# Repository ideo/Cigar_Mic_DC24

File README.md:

### Cigar Mic
Designed for DEF CON 24 to compliment the [Bender Badge by AND!XOR](https://github.com/ANDnXOR/ANDnXOR_DC24_Badge). The Cigar Mic adds an audio input to the Bender Badge in order to show a real-time spectrum anaysis of any activity occuring between 0 and 10kHz around the badge.

#### Configuration
Cigar mic requires 3.3V, GND, an ADC input pin, and three 3.3V output pins. The included software is compatible with AND!XOR’s Bender Badge and should be connected as follows:
```
OUT  -> PA1
GND  -> GND
3.3V -> 3.3V
L1   -> PA3
L2   -> PA4
L3   -> PA5
```

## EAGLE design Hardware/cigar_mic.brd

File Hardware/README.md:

### Cigar Mic Hardware
Schematic and layout created using [Eagle 7.4.0](https://cadsoft.io/)

The Cigar Mic is a fairly simple analog device comprised of a microphone, an amplifier, and a low pass filter. The cutoff frequency of the LPF is ~10kHz and the gain of the amplifier is 100. The circuit requires and 3.3V source, and the output signal is centered around ~1.65V.

The top side of the board includes 3 orange LEDs that run at 20mA each (this is very bright, and I’d suggest raising the value of their resistors, R7,8,9, to make the LEDs a little more subtle). These are positioned to make it look like the cigar is lit.

This layout differs slightly from what was released at DEF CON 24 in order to fix two errors with the original design. The first being the + and - flipped, hence the flywires soldered to these pins, and the other being the mic leads were flipped. Both of these were a result of quick design and not paying attention/double checking parts designed by others.

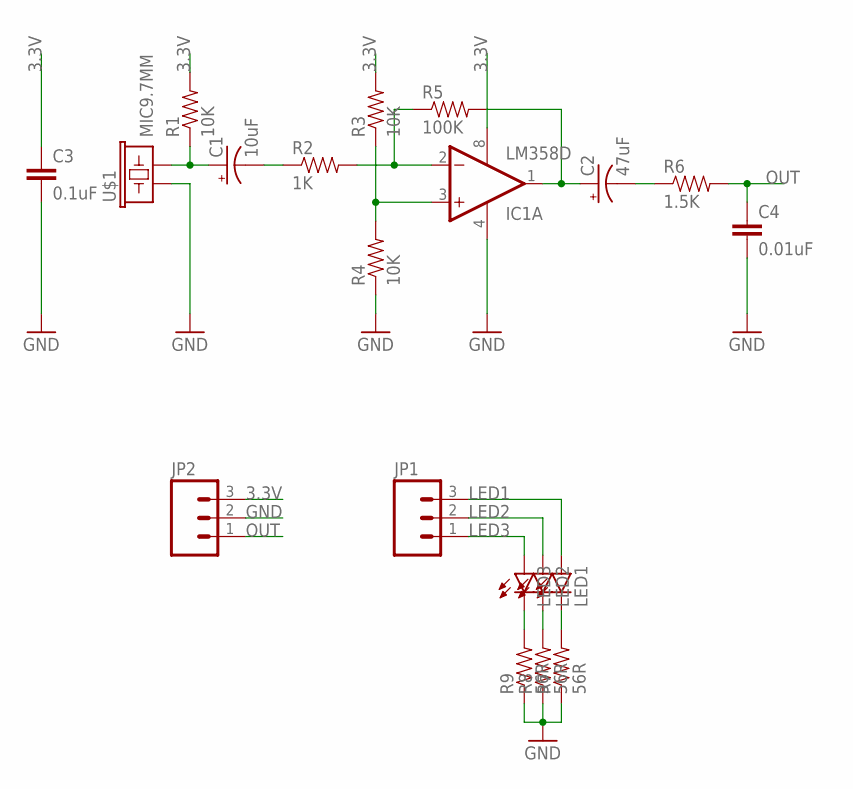
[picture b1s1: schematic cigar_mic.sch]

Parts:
C1: 10uF; POLAR
C2: 47uF; POLAR
C3: 0.1uF; 0805
C4: 0.01uF; 0805
IC1: LM358D; SO08
JP1, JP2: M031X03_NO_SILK; 1X03_NO_SILK
LED1, LED2, LED3: LED0603; LED-0603
R1, R3, R4: 10K; 0603-RES
R2: 1K; 0603-RES
R5: 100K; 0603-RES
R6: 1.5K; 0603-RES
R7, R8, R9: 56R; 0603-RES
U$1: MIC9.7MM; MIC-9.7MM

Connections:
3.3V: C3.1, IC1.8 (V+), JP2.3, R1.2, R3.2
GND: C3.2, C4.2, IC1.4 (V-), JP2.2, R4.1, R7.1, R8.1, R9.1, U$1.1
LED1: JP1.3, LED1.A
LED2: JP1.2, LED2.A
LED3: JP1.1, LED3.A
unnamed: C1.P$1 (+), R1.1, U$1.2
unnamed: C1.P$2 (-), R2.1
unnamed: IC1.2 (-IN), R2.2, R5.1
unnamed: IC1.3 (+IN), R3.1, R4.2
unnamed: C2.P$1 (+), IC1.1 (OUT), R5.2
unnamed: C2.P$2 (-), R6.1
unnamed: LED3.C, R9.2
unnamed: LED2.C, R8.2
unnamed: LED1.C, R7.2
OUT: C4.1, JP2.1, R6.2

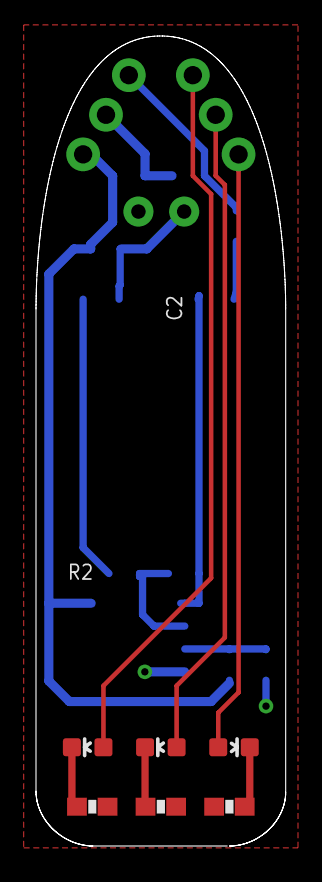
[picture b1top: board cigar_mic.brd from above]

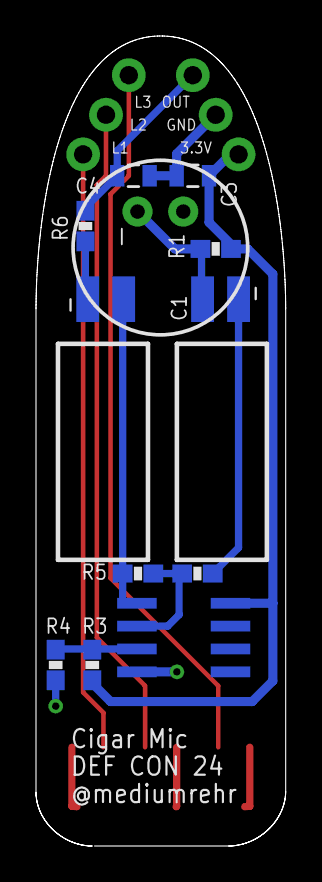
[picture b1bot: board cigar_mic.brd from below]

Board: 2 copper layers, 13.9 x 45.0 mm, 20 parts (12 on the bottom side), 15 nets.

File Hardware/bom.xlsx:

| Cigar Mic v1
 | Rob Rehr
 | DEF CON 24
 | Aug 4, 2016
 | Item | Reference | Package | Description | Manufacturer | Part # | Distributor | Distributor Part #
 |  | IC1 | 8-SO | IC OPAMP GP 1.1MHZ 8SO | STMicroelectronics | LM358DT | DigiKey | 497-1591-1-ND
 |  | U$1 | TH | 20Hz ~ 20kHz Analog Microphone Electret Condenser Omnidirectional (-44dB ±2dB @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 | CUI Inc | CMA-4544PF-W | DigiKey | 102-1721-ND
 |  | R1,3,4 | 603 | RES SMD 10K OHM 5% 1/4W 0603 | Rohm Semiconductor | ESR03EZPJ103 | DigiKey | RHM10KDCT-ND
 |  | R2 | 603 | RES SMD 1K OHM 5% 1/4W 0603 | Rohm Semiconductor | ESR03EZPJ102 | DigiKey | RHM1.0KDCT-ND
 |  | R5 | 603 | RES SMD 100K OHM 5% 1/4W 0603 | Rohm Semiconductor | ESR03EZPJ104 | DigiKey | RHM100KDCT-ND
 |  | R6 | 603 | RES SMD 1.5K OHM 5% 1/4W 0603 | Rohm Semiconductor | ESR03EZPJ152 | DigiKey | RHM1.5KDCT-ND
 |  | R7,8,9 | 603 | RES SMD 56 OHM 5% 1/4W 0603 | Rohm Semiconductor | ESR03EZPJ560 | DigiKey | RHM56DCT-ND
 |  | C1 | TH | 10µF 25V Aluminum Capacitors Radial, Can 1000 Hrs @ 85°C | Elna America | RFS-25V100ME3#5 | DigiKey | 604-1050-ND
 |  | C2 | TH | 47µF 6.3V Aluminum Capacitors Radial, Can 2000 Hrs @ 105°C | Nichicon | UKA0J470MDD1TD | DigiKey | 493-4626-1-ND
 |  | C3 | 805 | 0.10µF 50V Ceramic Capacitor X7R 0805 (2012 Metric) 0.079" L x 0.049" W (2.00mm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 | TDK Corporation | C2012X7R1H104K085AA | DigiKey | 445-7534-1-ND
 |  | C4 | 805 | 10000pF 250V Ceramic Capacitor JB 0805 (2012 Metric) 0.079" L x 0.049" W (2.00m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 | TDK Corporation | C2012JB2E103K125AA | DigiKey | 445-11562-1-ND

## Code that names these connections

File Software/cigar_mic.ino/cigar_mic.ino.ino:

////////////////////////////////////////////////////////////////////
//
//  Real-time spectrum analyzer for 0-20kHz
//   
//  Designed for DEF CON 24 and AND!XOR's Bender Badge
//
//  1024-point FFT
//  ~40kHz sampling rate
//
//  Hardware and software developed by rob rehr (@mediumrehr)
//  Last modified: Aug 16, 2016
//
//  To Do:
//  - find/fix the error with showing the audio wave in DFU mode
//  - further test windowing function
//  - integrate with AND!XOR Bender Badge code
//    - reduce SRAM usage
//
//  MIT License
//
//  Credits
//  FFT library written by STMicroelectronics
//  Software based on projects by Beherith and pingumacpenguin
//
////////////////////////////////////////////////////////////////////

//-FFT-------------------------------------------------------------------------
#define FFTLEN 1024
#define LOGSCALE 1 // display bins logarithmicallly
#define LINSCALE 0 // display bins linearly
#include <cr4_fft_1024_stm32.h>
uint16_t data16[FFTLEN];
uint32_t data32[FFTLEN];
uint32_t y[FFTLEN];
uint16_t hammingwindow[FFTLEN/2];
// my best attempt at logarithmically spacing 511 bins
uint16_t logBins[32] = {0,1,2,3,4,5,6,7,8,9,10,11,12,13,15,18,22,27,33,40,49,59,72,87,106,129,156,190,230,280,340,413};
uint16_t logBinsGap[32] = {1,1,1,1,1,1,1,1,1,1,1,1,1,2,3,4,5,6,7,9,10,13,15,19,23,27,34,40,50,60,73,98};
uint16_t FFTMode = 1; // 1 for frequecy display; 0 for amplitude display

//-Display---------------------------------------------------------------------
#include <Adafruit_GFX_AS.h>
#include <Adafruit_SSD1306_STM32.h>
#include <SPI.h>

#define SCREENWIDTH 128
#define SCREENHEIGHT 64

#define OLED_MOSI  PB15
#define OLED_CLK   PB13
#define OLED_DC    PB3
#define OLED_CS    PB12
#define OLED_RESET PB4
Adafruit_SSD1306 display(OLED_MOSI, OLED_CLK, OLED_DC, OLED_RESET, OLED_CS);

//-DMA-------------------------------------------------------------------------
volatile static bool dma1_ch1_Active;
#include <libmaple/pwr.h>
#include <libmaple/scb.h>
#include <libmaple/rcc.h>
#include <libmaple/adc.h>

//-Other-----------------------------------------------------------------------
// cigar LEDs
#define LED1 PA3
#define LED2 PA4
#define LED3 PA5
#define LEDThresh 200
const int8_t analogInPin = PA1;
uint16_t ampWave[SCREENWIDTH] = {0};

void init_hamming_window(uint16_t *windowtarget, int len) {
  for(int i=0; i<len/2; i++){ windowtarget[i] = (0.54-0.46*cos((2*i*3.141592)/(len-1)))*65536; }
}

// not certain windowing is working correctly. more testing is needed
void window(uint32_t *data, uint16_t *weights, int len, int scale) {
  for(int i=0; i<len; i++){
    int weight_index = i;
    if(i >= len/2) weight_index = (len-1)-i;
    data[i] = ((data[i]*scale*weights[weight_index]) >> 16) & 0xFFFF;
  }
}

uint16_t asqrt(uint32_t x) {
  /*   From http://medialab.freaknet.org/martin/src/sqrt/sqrt.c
   *   Logically, these are unsigned. We need the sign bit to test
   *   whether (op - res - one) underflowed.
   *   good enough precision; 10x faster than regular sqrt
   */
  int32_t op, res, one;

  op = x;
  res = 0;
  /* "one" starts at the highest power of four <= than the argument. */
  one = 1 << 30;   /* second-to-top bit set */
  while(one > op) one >>= 2;
  while(one != 0) {
    if(op >= res+one) {
      op = op-(res+one);
      res = res+2*one;
    }
    res /= 2;
    one /= 4;
  }
  return (uint16_t)(res);
}

void fill(uint32_t *data, uint32_t value, int len) {
  for(int i=0; i<len; i++) { data[i] = value; }
}

void fill(uint16_t *data, uint32_t value, int len) {
  for(int i=0; i<len; i++) { data[i] = value; }
}

void real_to_complex(uint16_t *in, uint32_t *out, int len) {
  for(int i=0; i<len; i++) { out[i] = in[i]*8; }
}

void setADCs () {
  rcc_set_prescaler(RCC_PRESCALER_ADC, RCC_ADCPRE_PCLK_DIV_8 );

  int pinMapADCin = PIN_MAP[analogInPin].adc_channel;
  adc_set_sample_rate(ADC1, ADC_SMPR_239_5); // ~37.65 khz sample rate
 
  adc_set_reg_seqlen(ADC1, 1);
  ADC1->regs->SQR3 = pinMapADCin;
  ADC1->regs->CR2 |= ADC_CR2_CONT; // set continuous mode
  ADC1->regs->CR2 |= ADC_CR2_SWSTART; // regular channels
}

static void DMA1_CH1_Event() {
  dma1_ch1_Active = 0;
}

void adc_dma_enable(const adc_dev *dev) {
  bb_peri_set_bit(&dev->regs->CR2, ADC_CR2_DMA_BIT, 1);
}

void takeSamples() {
  if(FFTMode) {
    // perform DMA, 
    dma_init(DMA1);
    dma_attach_interrupt(DMA1, DMA_CH1, DMA1_CH1_Event);

    adc_dma_enable(ADC1);
    dma_setup_transfer(DMA1, DMA_CH1, &ADC1->regs->DR, DMA_SIZE_16BITS, data16, DMA_SIZE_16BITS, (DMA_MINC_MODE | DMA_TRNS_CMPLT)); // receive buffer DMA
    dma_set_num_transfers(DMA1, DMA_CH1, FFTLEN);
    dma1_ch1_Active = 1;
  
    dma_enable(DMA1, DMA_CH1); // enable the channel and start the transfer.
    uint32_t time_left_in_dma = micros();
  
    while(dma1_ch1_Active){ }; // wait for the DMA to complete
    dma_disable(DMA1, DMA_CH1); // end of trasfer, disable DMA and continuous mode.
    real_to_complex(data16, data32, FFTLEN);
    perform_fft(data32, y, FFTLEN);
    displayBins(y, FFTLEN, LOGSCALE);
  } else {
    // only works for serial upload. doesn't work with DFU mode for some reason
    int analogIn = analogRead(analogInPin);
    displayWave(analogIn);
  }
}

void setup() {
  // enable Serial
  Serial.begin(115200); // only works with serial upload mode
  
  // initialize the display
  display.begin(SSD1306_SWITCHCAPVCC);
  display.clearDisplay();
  display.display();

  // initialize FFT variables
  init_hamming_window(hammingwindow, FFTLEN);
  fill(y,0,FFTLEN);
  fill(data32,1,FFTLEN);
  fill(data16,1,FFTLEN);

  // calibrate and setup ADC
  adc_calibrate(ADC1);
  setADCs();

  // initialize cigar LEDs
  pinMode(LED1, OUTPUT);
  pinMode(LED2, OUTPUT);
  pinMode(LED3, OUTPUT);
  digitalWrite(LED1, LOW);
  digitalWrite(LED2, LOW);
  digitalWrite(LED3, LOW);
}

void inplace_magnitude(uint32_t *target, uint16_t len){
  uint16_t * p16;
  for(int i=0; i<len; i++){
     int16_t real = target[i] & 0xFFFF;
     int16_t imag = target[i] >> 16;
     uint32_t magnitude = asqrt(real*real + imag*imag);
     target[i] = magnitude; 
  }
}
  
uint32_t perform_fft(uint32_t *indata, uint32_t *outdata, const int len){
	uint32_t timetaken = micros();
//	window(indata,hammingwindow,len,1); //scaling factor of 4 for 4095> 16 bits
	cr4_fft_1024_stm32(outdata, indata, len);
	inplace_magnitude(outdata, len);
	return micros() - timetaken;
}

// dispaly audio as an amplitude wave
// only works with serial upload mode
void displayWave(uint16_t newAnalog) {
  display.clearDisplay();
  // move previous amplitudes forward
  for(int i=(SCREENWIDTH-1); i>0; i--) {
    display.drawLine(i, (32-ampWave[i-1]), i, (32+ampWave[i-1]), WHITE);
    ampWave[i] = ampWave[i-1];
  }
  // append newest applitude
  int newAmp = newAnalog*SCREENHEIGHT/4096;
  newAmp -= 32;
  display.drawLine(0, 32-newAmp, 0, 32+newAmp, WHITE);
  ampWave[0] = newAmp;
  display.display();
}

// display audio as bin levels after FFT
void displayBins(uint32_t *data, int len, bool scale) {
  uint32_t maxvalue = 1024;
  uint32_t myBins[32] = {0};
  uint32_t LED1Max = 0;
  uint32_t LED2Max = 0;
  uint32_t LED3Max = 0;
  if(scale) {
    // logarithmic x axis
    for(int i=0; i<32; i++) {
      myBins[i] = 0;
      for(int j=0; j<logBinsGap[i]; j++) {
        int newData = data[logBins[i]+j];
        myBins[i] = max(myBins[i], newData);
      }
    }
  } else {
    // linear x axis
    for(int i=0; i<32; i++) {
      myBins[i] = 0;
      for(int j=0; j<16; j++) {
        myBins[i] = max(myBins[i], data[(i*32)+j]);
      }
    }
  }
  display.clearDisplay();
  // we toss the first bin since it's 0Hz
  for(int i=1; i< 32; i++) {
    float FFTBarHeight = myBins[i]*SCREENHEIGHT/maxvalue;
    int startXPos = 4*(31-i);
    display.drawLine(startXPos+0, 0, startXPos+0, (int)FFTBarHeight, WHITE);
    display.drawLine(startXPos+1, 0, startXPos+1, (int)FFTBarHeight, WHITE);
    display.drawLine(startXPos+2, 0, startXPos+2, (int)FFTBarHeight, WHITE);
    display.drawLine(startXPos+3, 0, startXPos+3, (int)FFTBarHeight, WHITE);

    if(i < 11) {
      if(LED1Max < myBins[i]) LED1Max = myBins[i];
    } else {
      if(i < 21) {
        if(LED2Max < myBins[i]) LED2Max = myBins[i];
      } else {
        if(LED3Max < myBins[i]) LED3Max = myBins[i];
      }
    }
  }
  
  display.display();

  // turn cigar LEDs on/off depending on bin levels
  if(LED1Max > LEDThresh) {
    digitalWrite(LED1, HIGH);
  } else {
    digitalWrite(LED1, LOW);
  }
  if(LED2Max > LEDThresh) {
    digitalWrite(LED2, HIGH);
  } else {
    digitalWrite(LED2, LOW);
  }
  if(LED3Max > LEDThresh) {
    digitalWrite(LED3, HIGH);
  } else {
    digitalWrite(LED3, LOW);
  }
}

void loop() { 
  while(1){ // loop seems to run only once, hence the while 
	  takeSamples();
  }
}

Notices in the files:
parts and their libraries:
SparkFun-Capacitors: Licensing: Creative Commons ShareAlike 4.0 International - https://creativecommons.org/licenses/by-sa/4.0
